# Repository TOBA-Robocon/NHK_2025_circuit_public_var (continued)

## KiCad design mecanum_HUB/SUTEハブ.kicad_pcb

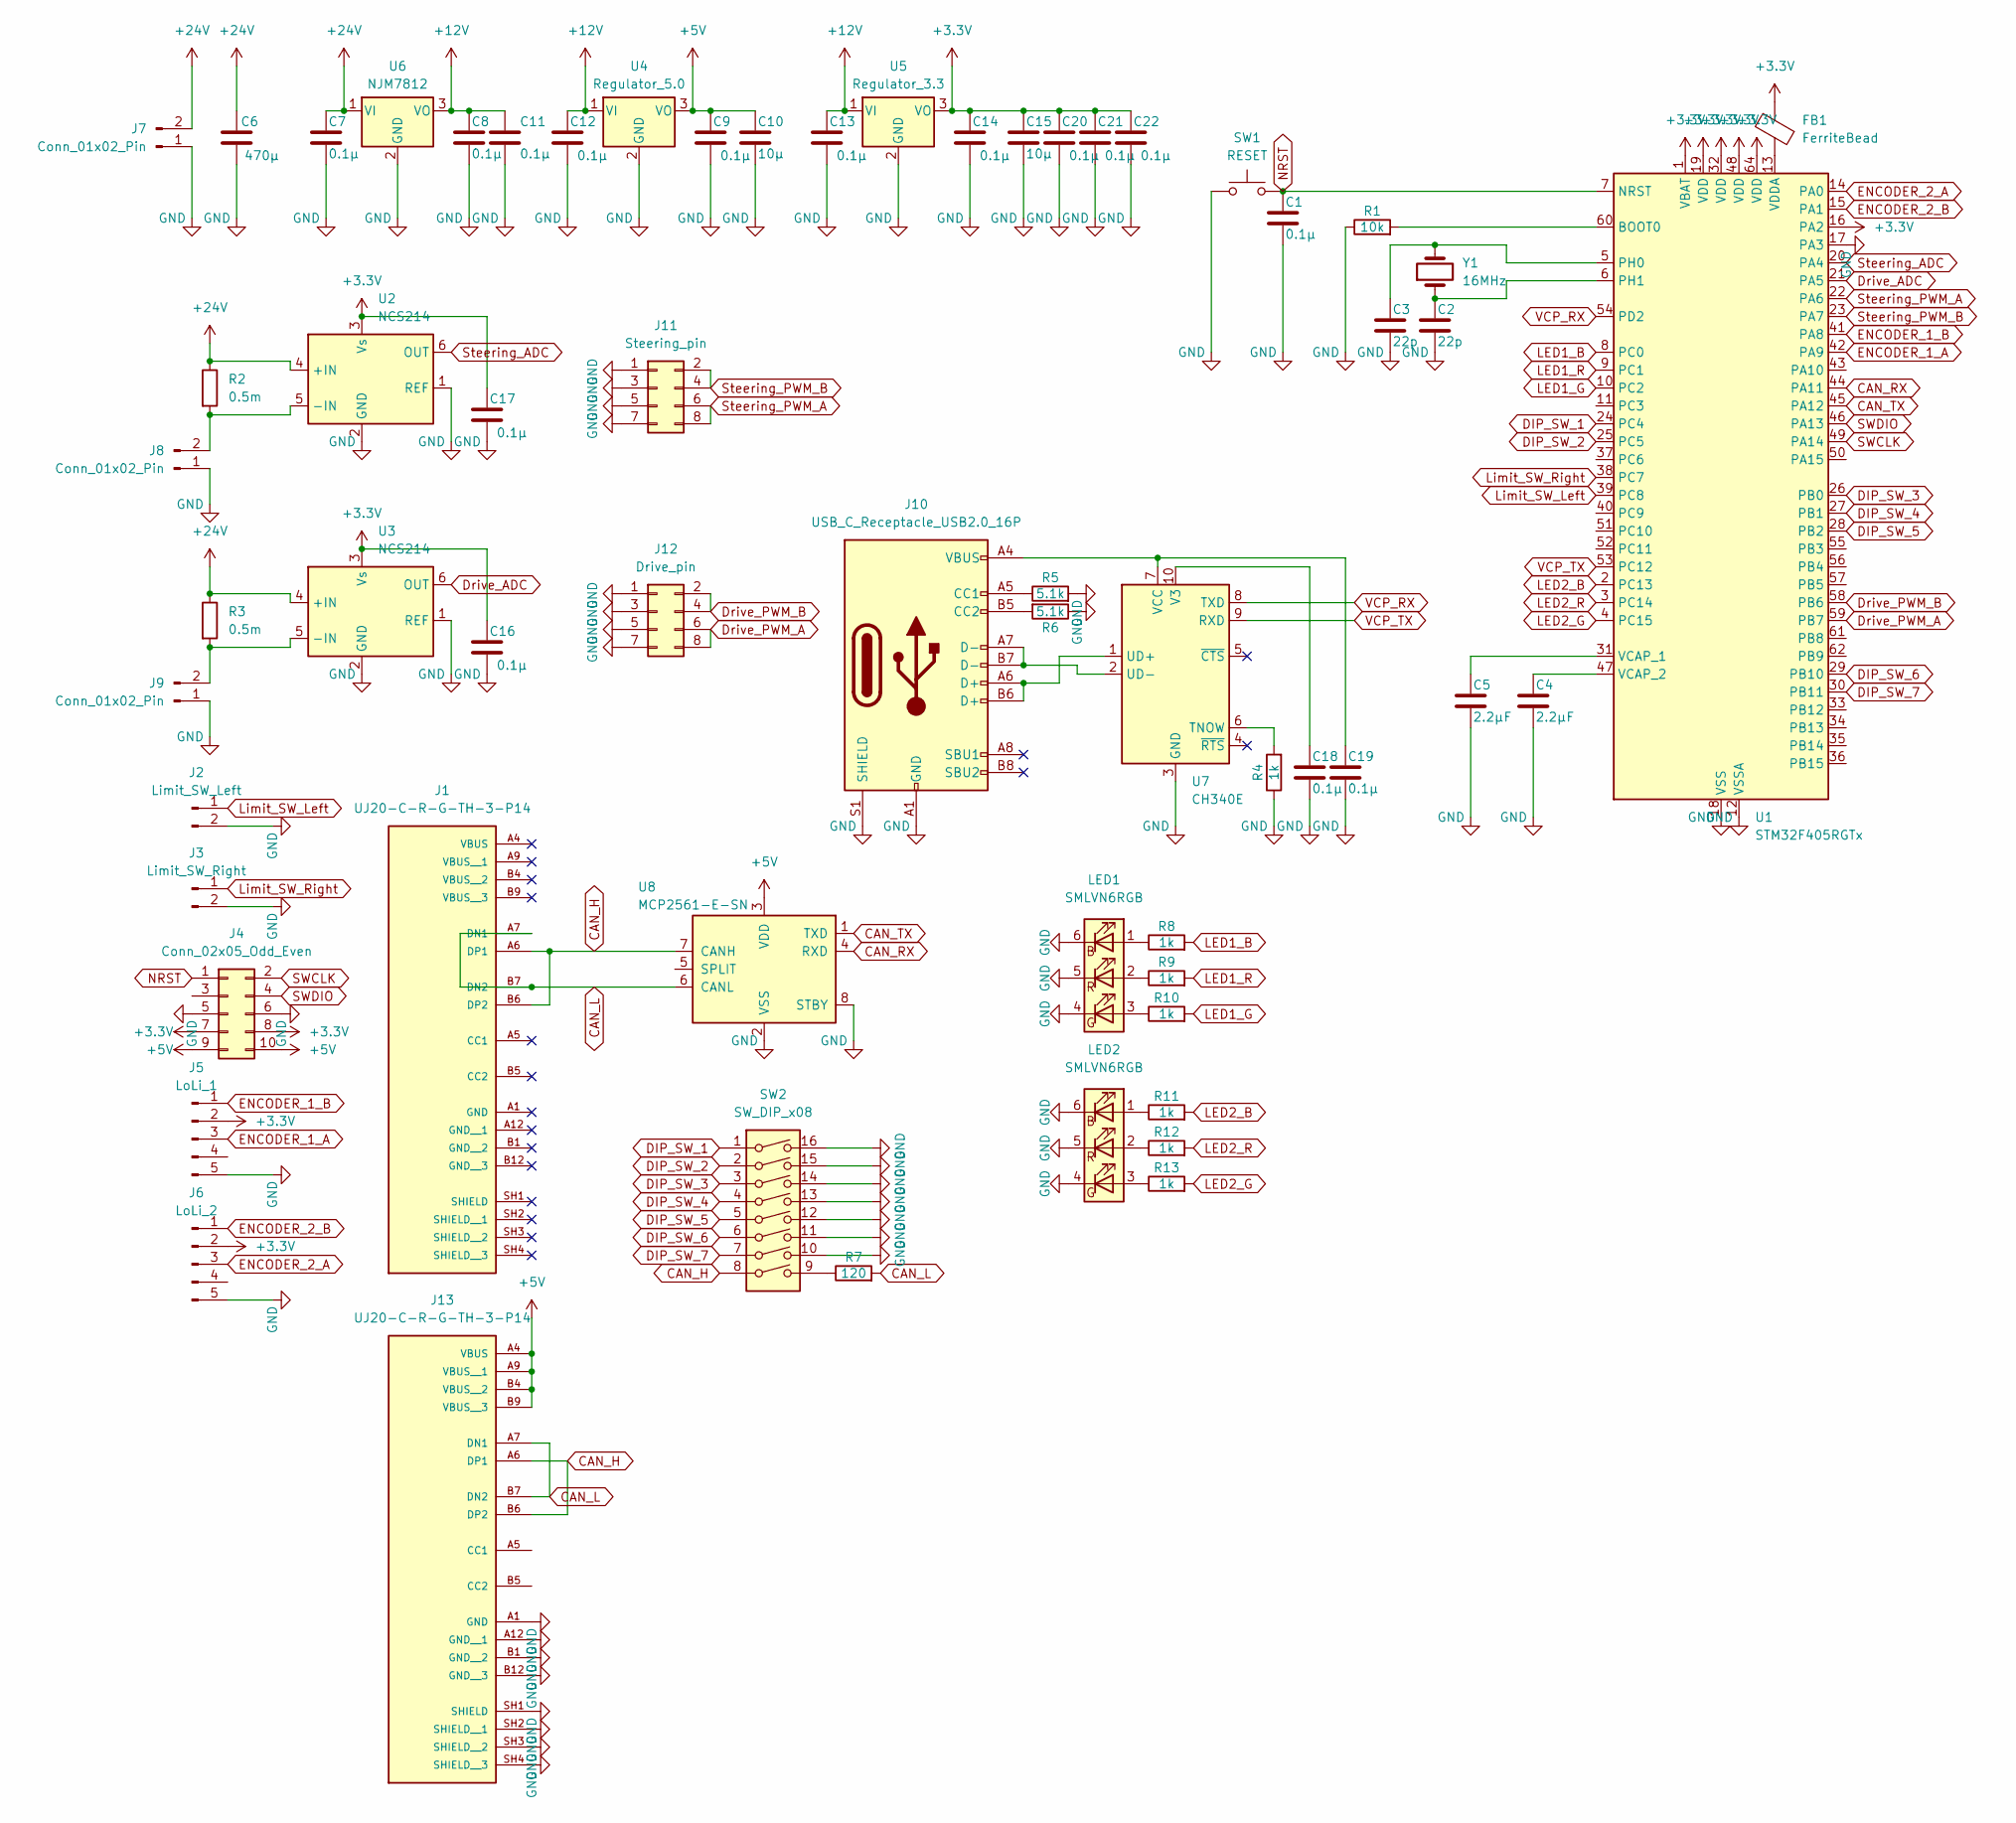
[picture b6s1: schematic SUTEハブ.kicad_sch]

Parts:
C1, C7, C8, C9, C11, C12, C13, C14, C16, C17, C18, C19, C20, C21, C22: 0.1μ; C_0603_1608Metric_Pad1.08x0.95mm_HandSolder
C2, C3: 22p; C_0603_1608Metric_Pad1.08x0.95mm_HandSolder
C4, C5: 2.2μF; C_0603_1608Metric_Pad1.08x0.95mm_HandSolder
C6: 470μ; CP_Radial_D8.0mm_P5.00mm
C10, C15: 10μ; C_0603_1608Metric_Pad1.08x0.95mm_HandSolder
FB1: FerriteBead; L_0805_2012Metric_Pad1.05x1.20mm_HandSolder
J1, J13: UJ20-C-R-G-TH-3-P14; SAMESKY_UJ20-C-R-G-TH-3-P14; PARTREV 1.0
J2: Limit_SW_Left; JST_XA_B02B-XASK-1_1x02_P2.50mm_Vertical
J3: Limit_SW_Right; JST_XA_B02B-XASK-1_1x02_P2.50mm_Vertical
J4: Conn_02x05_Odd_Even; IDC-Header_2x05_P2.54mm_Vertical
J5: LoLi_1; JST_XA_B05B-XASK-1_1x05_P2.50mm_Vertical
J6: LoLi_2; JST_XA_B05B-XASK-1_1x05_P2.50mm_Vertical
J7: Conn_01x02_Pin; AMASS_XT60PW-M_1x02_P7.20mm_Horizontal
J8, J9: Conn_01x02_Pin; AMASS_XT60-F_1x02_P7.20mm_Vertical
J10: USB_C_Receptacle_USB2.0_16P; USB_C_Receptacle_HRO_TYPE-C-31-M-12
J11: Steering_pin; PinSocket_2x04_P2.54mm_Vertical
J12: Drive_pin; PinSocket_2x04_P2.54mm_Vertical
LED1, LED2: SMLVN6RGB; LED_ROHM_SMLVN6
R1: 10k; R_0603_1608Metric_Pad0.98x0.95mm_HandSolder
R2, R3: 0.5m; R_2512_6332Metric
R4, R8, R9, R10, R11, R12, R13: 1k; R_0603_1608Metric_Pad0.98x0.95mm_HandSolder
R5, R6: 5.1k; R_0603_1608Metric_Pad0.98x0.95mm_HandSolder
R7: 120; R_0603_1608Metric_Pad0.98x0.95mm_HandSolder
SW1: RESET; SW_PUSH_6mm
SW2: SW_DIP_x08; DIP-16_W7.62mm
U1: STM32F405RGTx; LQFP-64_10x10mm_P0.5mm
U2, U3: NCS214; SOT-363_SC-70-6_Handsoldering
U4: Regulator_5.0; TO-252-2
U5: Regulator_3.3; TO-252-2
U6: NJM7812; TO-252-2
U7: CH340E; MSOP-10_3x3mm_P0.5mm
U8: MCP2561-E-SN; SOIC-8_3.9x4.9mm_P1.27mm
Y1: 16MHz; Crystal_HC18-U_Vertical

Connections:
+3.3V: C14.1, C15.1, C16.1, C17.1, C20.1, C21.1, C22.1, FB1.2, J4.7, J4.8, J5.2, J6.2, U1.1 (VBAT), U1.16 (PA2), U1.19 (VDD), U1.32 (VDD), U1.48 (VDD), U1.64 (VDD), U2.3 (Vs), U3.3 (Vs), U5.3 (VO)
+5V: C9.1, C10.1, J4.9, J4.10, J13.A4 (VBUS), J13.A9 (VBUS__1), J13.B4 (VBUS__2), J13.B9 (VBUS__3), U4.3 (VO), U8.3 (VDD)
+12V: C8.1, C11.1, C12.1, C13.1, U4.1 (VI), U5.1 (VI), U6.3 (VO)
+24V: C6.1, C7.1, J7.2, R2.1, R3.1, U2.4 (+IN), U3.4 (+IN), U6.1 (VI)
CAN_H: J1.A6 (DP1), J1.B6 (DP2), J13.A6 (DP1), J13.B6 (DP2), SW2.8, U8.7 (CANH)
CAN_L: J1.A7 (DN1), J1.B7 (DN2), J13.A7 (DN1), J13.B7 (DN2), R7.2, U8.6 (CANL)
CAN_RX: U1.44 (PA11), U8.4 (RXD)
CAN_TX: U1.45 (PA12), U8.1 (TXD)
DIP_SW_1: SW2.1, U1.24 (PC4)
DIP_SW_2: SW2.2, U1.25 (PC5)
DIP_SW_3: SW2.3, U1.26 (PB0)
DIP_SW_4: SW2.4, U1.27 (PB1)
DIP_SW_5: SW2.5, U1.28 (PB2)
DIP_SW_6: SW2.6, U1.29 (PB10)
DIP_SW_7: SW2.7, U1.30 (PB11)
Drive_ADC: U1.21 (PA5), U3.6 (OUT)
Drive_PWM_A: J12.6, J12.8, U1.59 (PB7)
Drive_PWM_B: J12.2, J12.4, U1.58 (PB6)
ENCODER_1_A: J5.3, U1.42 (PA9)
ENCODER_1_B: J5.1, U1.41 (PA8)
ENCODER_2_A: J6.3, U1.14 (PA0)
ENCODER_2_B: J6.1, U1.15 (PA1)
GND: C1.2, C2.2, C3.2, C4.2, C5.2, C6.2, C7.2, C8.2, C9.2, C10.2, C11.2, C12.2, C13.2, C14.2, C15.2, C16.2, C17.2, C18.2, C19.2, C20.2, C21.2, C22.2, J2.2, J3.2, J4.5, J4.6, J5.5, J6.5, J7.1, J8.1, J9.1, J10.A1 (GND), J10.A12 (GND), J10.B1 (GND), J10.B12 (GND), J10.S1 (SHIELD), J11.1, J11.3, J11.5, J11.7, J12.1, J12.3, J12.5, J12.7, J13.A1 (GND), J13.A12 (GND__1), J13.B1 (GND__2), J13.B12 (GND__3), J13.SH1 (SHIELD), J13.SH2 (SHIELD__1), J13.SH3 (SHIELD__2), J13.SH4 (SHIELD__3), LED1.4 (GK), LED1.5 (RK), LED1.6 (BK), LED2.4 (GK), LED2.5 (RK), LED2.6 (BK), R1.1, R4.1, R5.2, R6.1, SW1.1, SW2.10, SW2.11, SW2.12, SW2.13, SW2.14, SW2.15, SW2.16, U1.12 (VSSA), U1.17 (PA3), U1.18 (VSS), U1.63 (VSS), U2.1 (REF), U2.2 (GND), U3.1 (REF), U3.2 (GND), U4.2 (GND), U5.2 (GND), U6.2 (GND), U7.3 (GND), U8.2 (VSS), U8.8 (STBY)
LED1_B: R8.2, U1.8 (PC0)
LED1_G: R10.2, U1.10 (PC2)
LED1_R: R9.2, U1.9 (PC1)
LED2_B: R11.2, U1.2 (PC13)
LED2_G: R13.2, U1.4 (PC15)
LED2_R: R12.2, U1.3 (PC14)
Limit_SW_Left: J2.1, U1.39 (PC8)
Limit_SW_Right: J3.1, U1.38 (PC7)
NRST: C1.1, J4.1, SW1.2, U1.7 (NRST)
unnamed: J8.2, R2.2, U2.5 (-IN)
unnamed: J9.2, R3.2, U3.5 (-IN)
unnamed: J10.A5 (CC1), R5.1
unnamed: J10.B5 (CC2), R6.2
unnamed: LED1.1 (BA), R8.1
unnamed: LED1.3 (GA), R10.1
unnamed: LED1.2 (RA), R9.1
unnamed: LED2.1 (BA), R11.1
unnamed: LED2.3 (GA), R13.1
unnamed: LED2.2 (RA), R12.1
unnamed: R7.1, SW2.9
unnamed: R1.2, U1.60 (BOOT0)
unnamed: C3.1, U1.5 (PH0), Y1.2
unnamed: C2.1, U1.6 (PH1), Y1.1
unnamed: C5.1, U1.31 (VCAP_1)
unnamed: C4.1, U1.47 (VCAP_2)
unnamed: FB1.1, U1.13 (VDDA)
unnamed: R4.2, U7.6 (TNOW)
unnamed: J10.A6 (D+), J10.B6 (D+), U7.1 (UD+)
unnamed: J10.A7 (D-), J10.B7 (D-), U7.2 (UD-)
unnamed: C18.1, U7.10 (V3)
unnamed: C19.1, J10.A4 (VBUS), J10.A9 (VBUS), J10.B4 (VBUS), J10.B9 (VBUS), U7.7 (VCC)
SWCLK: J4.2, U1.49 (PA14)
SWDIO: J4.4, U1.46 (PA13)
Steering_ADC: U1.20 (PA4), U2.6 (OUT)
Steering_PWM_A: J11.6, J11.8, U1.22 (PA6)
Steering_PWM_B: J11.2, J11.4, U1.23 (PA7)
VCP_RX: U1.54 (PD2), U7.8 (TXD)
VCP_TX: U1.53 (PC12), U7.9 (RXD)

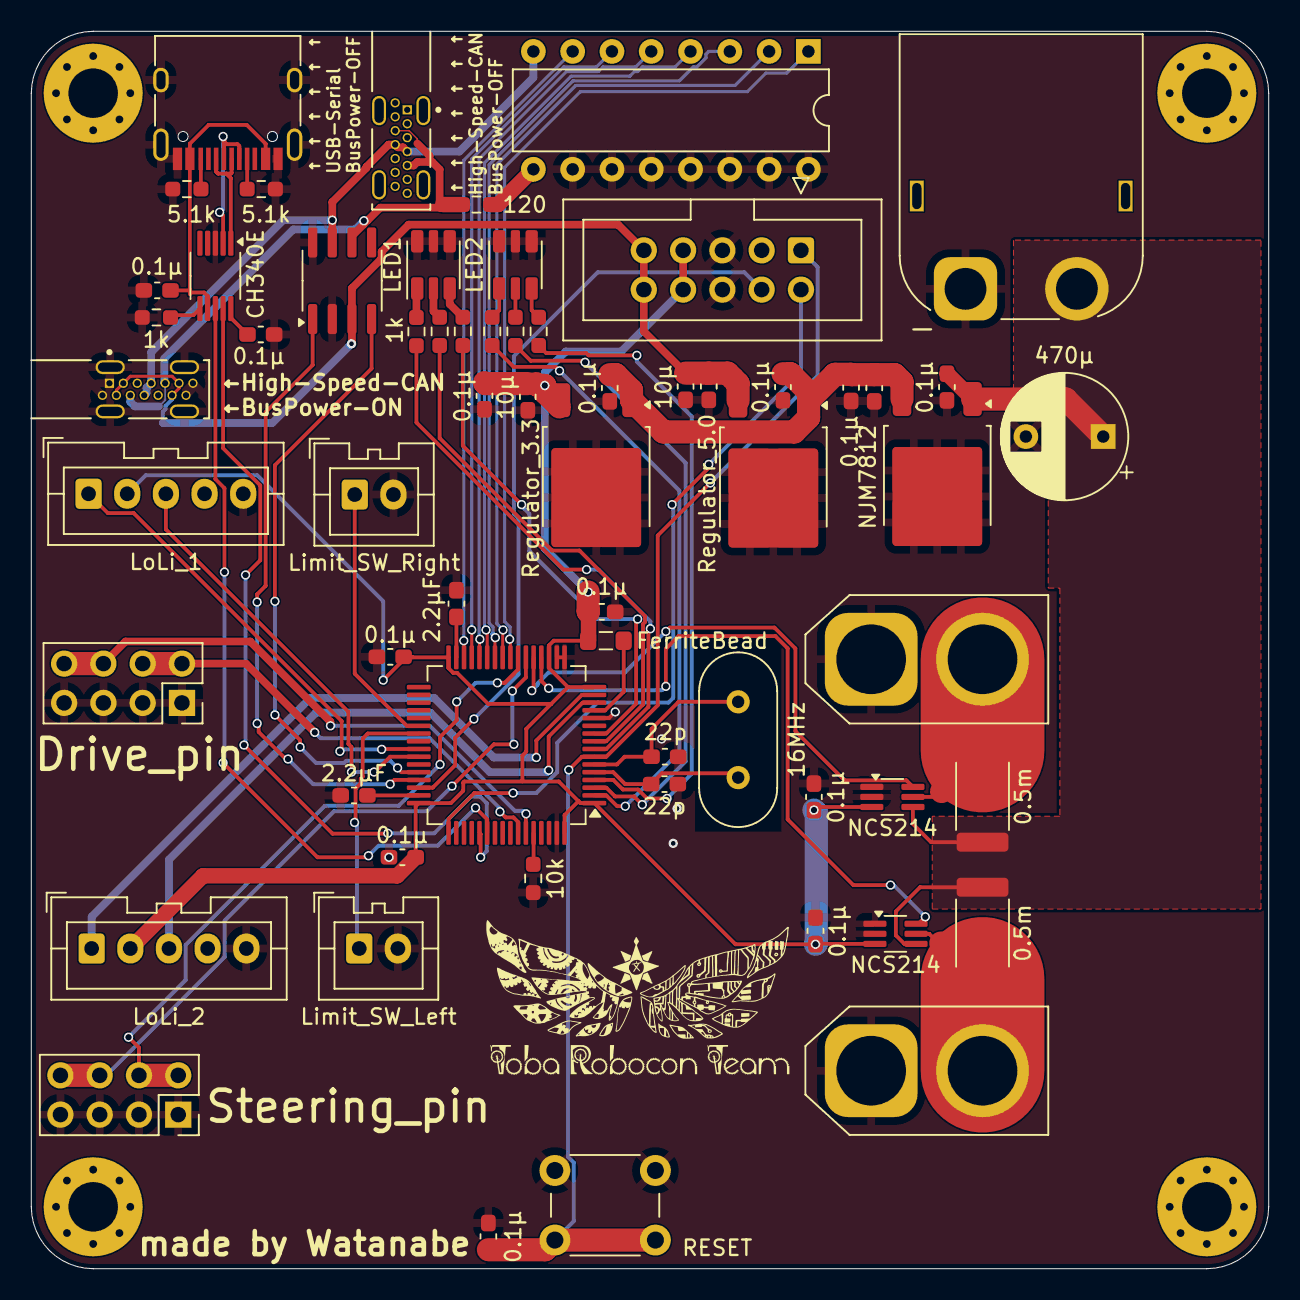
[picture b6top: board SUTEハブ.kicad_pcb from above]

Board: 2 copper layers, 80.0 x 80.0 mm, 62 parts (0 on the bottom side), 61 nets.

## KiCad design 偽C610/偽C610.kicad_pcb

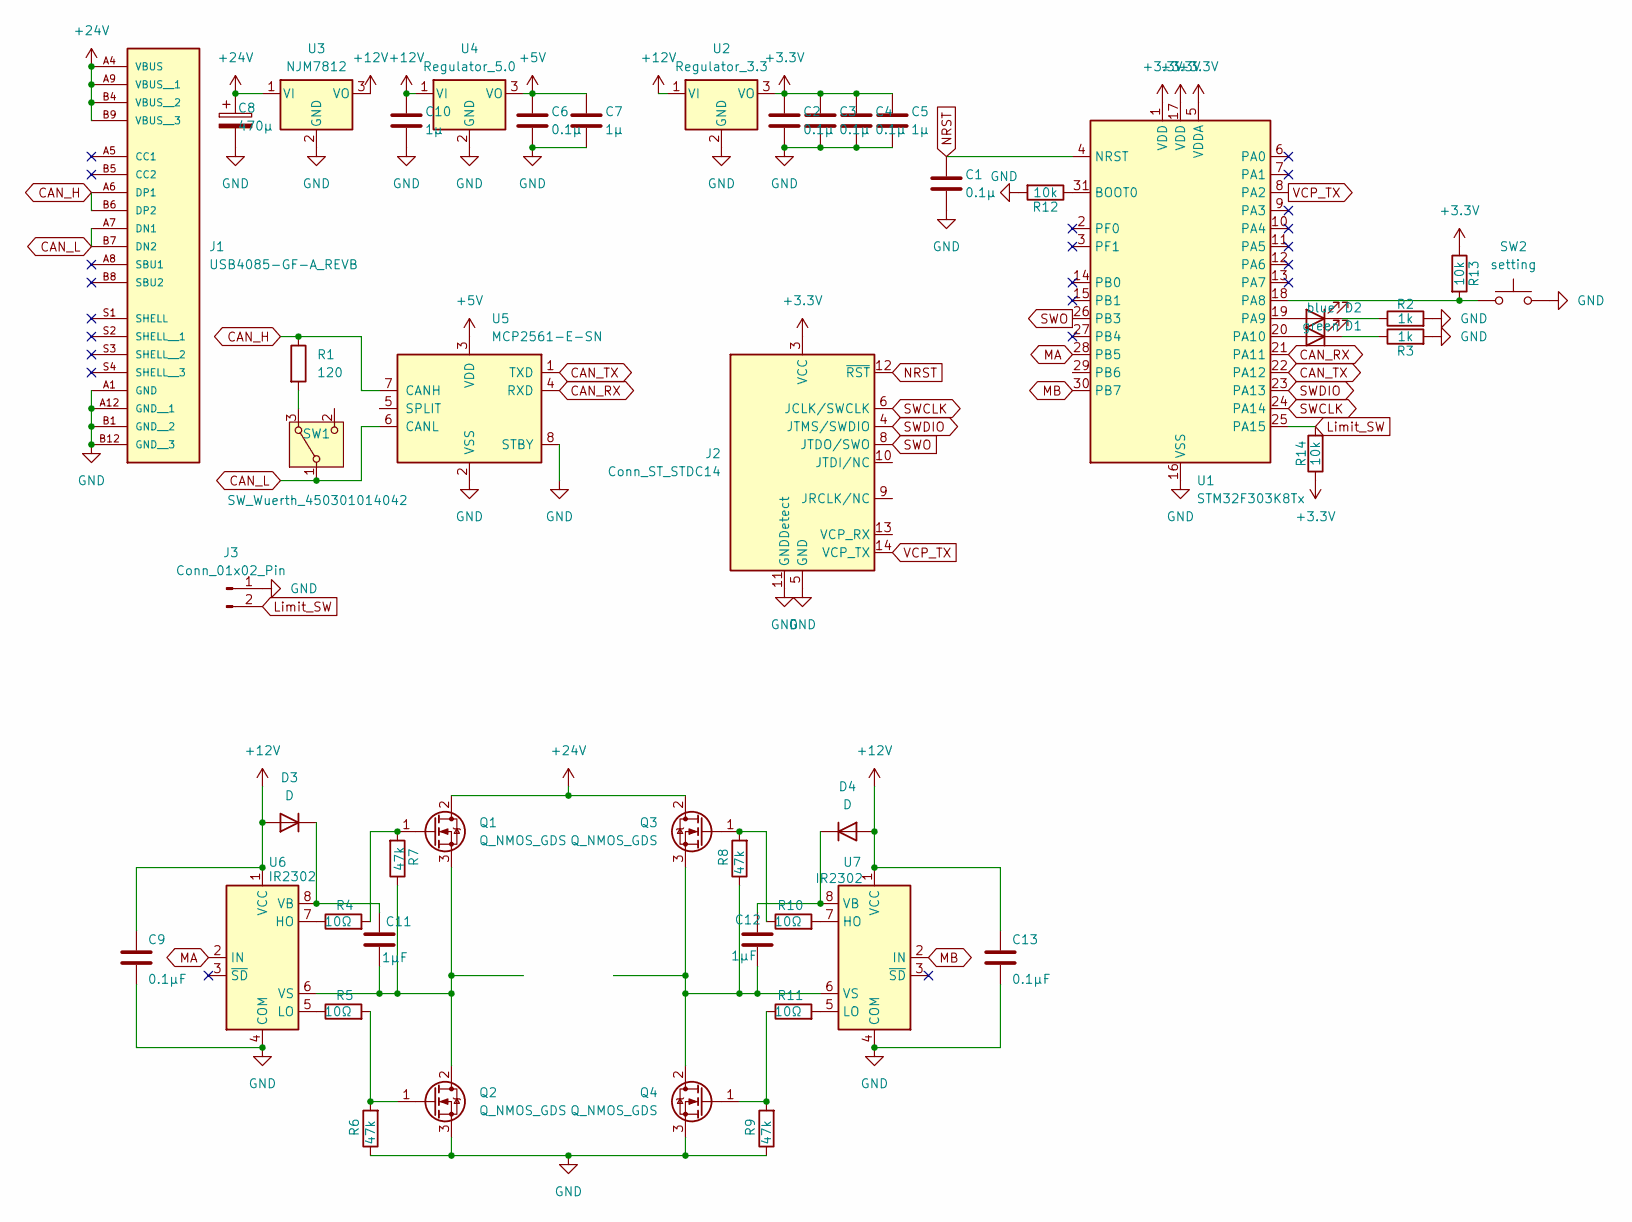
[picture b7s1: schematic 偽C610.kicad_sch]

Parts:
C1, C2, C3, C4, C6: 0.1μ; C_0603_1608Metric
C5, C7, C10: 1μ; C_0603_1608Metric
C8: 470μ; CP_Radial_D8.0mm_P3.50mm
C9, C13: 0.1μF; C_0603_1608Metric_Pad1.08x0.95mm_HandSolder
C11, C12: 1μF; C_0603_1608Metric_Pad1.08x0.95mm_HandSolder
D1: green; LED_0603_1608Metric
D2: blue; LED_0603_1608Metric
D3, D4: D; D_SOD-123F
J1: USB4085-GF-A_REVB; GCT_USB4085-GF-A_REVB; PARTREV B
J2: Conn_ST_STDC14; PinHeader_2x07_P1.27mm_Vertical
J3: Conn_01x02_Pin; JST_PH_B2B-PH-SM4-TB_1x02-1MP_P2.00mm_Vertical
Q1, Q2, Q3, Q4: Q_NMOS_GDS; TO-252-2
R1: 120; R_0603_1608Metric
R2, R3: 1k; R_0603_1608Metric
R4, R5, R10, R11: 10Ω; R_0603_1608Metric_Pad0.98x0.95mm_HandSolder
R6, R7, R8, R9: 47k; R_0603_1608Metric_Pad0.98x0.95mm_HandSolder
R12, R13, R14: 10k; R_0603_1608Metric
SW1: SW_Wuerth_450301014042; SW_Slide-03_Wuerth-WS-SLTV_10x2.5x6.4_P2.54mm
SW2: setting; SW_PUSH_1P1T_6x3.5mm_H5.0_APEM_MJTP1250
U1: STM32F303K8Tx; LQFP-32_7x7mm_P0.8mm
U2: Regulator_3.3; TO-252-2
U3: NJM7812; TO-252-2
U4: Regulator_5.0; TO-252-2
U5: MCP2561-E-SN; SOIC-8_3.9x4.9mm_P1.27mm
U6, U7: IR2302; SOIC-8_3.9x4.9mm_P1.27mm

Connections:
+3.3V: C2.1, C3.1, C4.1, C5.1, J2.3 (VCC), R13.1, R14.1, U1.1 (VDD), U1.5 (VDDA), U1.17 (VDD), U2.3 (VO)
+5V: C6.1, C7.1, U4.3 (VO), U5.3 (VDD)
+12V: C9.1, C10.1, C13.1, D3.2 (A), D4.2 (A), U2.1 (VI), U3.3 (VO), U4.1 (VI), U6.1 (VCC), U7.1 (VCC)
+24V: C8.1, J1.A4 (VBUS), J1.A9 (VBUS__1), J1.B4 (VBUS__2), J1.B9 (VBUS__3), Q1.2 (D), Q3.2 (D), U3.1 (VI)
CAN_H: J1.A6 (DP1), J1.B6 (DP2), R1.1, U5.7 (CANH)
CAN_L: J1.A7 (DN1), J1.B7 (DN2), SW1.1 (B), U5.6 (CANL)
CAN_RX: U1.21 (PA11), U5.4 (RXD)
CAN_TX: U1.22 (PA12), U5.1 (TXD)
GND: C1.2, C2.2, C3.2, C4.2, C5.2, C6.2, C7.2, C8.2, C9.2, C10.2, C13.2, J1.A1 (GND), J1.A12 (GND__1), J1.B1 (GND__2), J1.B12 (GND__3), J2.5 (GND), J2.7 (GND), J2.11 (GNDDetect), J3.1, Q2.3 (S), Q4.3 (S), R2.2, R3.2, R6.1, R9.1, R12.2, SW2.2, U1.16 (VSS), U1.32 (VSS), U2.2 (GND), U3.2 (GND), U4.2 (GND), U5.2 (VSS), U5.8 (STBY), U6.4 (COM), U7.4 (COM)
Limit_SW: J3.2, R14.2, U1.25 (PA15)
MA: U1.28 (PB5), U6.2 (IN)
MB: U1.30 (PB7), U7.2 (IN)
NRST: C1.1, J2.12 (~RST), U1.4 (NRST)
unnamed: D1.2 (A), U1.20 (PA10)
unnamed: D1.1 (K), R3.1
unnamed: D2.2 (A), U1.19 (PA9)
unnamed: D2.1 (K), R2.1
unnamed: C11.1, D3.1 (K), U6.8 (VB)
unnamed: C12.1, D4.1 (K), U7.8 (VB)
unnamed: Q1.1 (G), R4.2, R7.2
unnamed: C11.2, Q1.3 (S), Q2.2 (D), R7.1, U6.6 (VS)
unnamed: Q2.1 (G), R5.2, R6.2
unnamed: Q3.1 (G), R8.2, R10.1
unnamed: C12.2, Q3.3 (S), Q4.2 (D), R8.1, U7.6 (VS)
unnamed: Q4.1 (G), R9.2, R11.1
unnamed: R1.2, SW1.3 (A)
unnamed: R12.1, U1.31 (BOOT0)
unnamed: R13.2, SW2.1, U1.18 (PA8)
unnamed: R4.1, U6.7 (HO)
unnamed: R5.1, U6.5 (LO)
unnamed: R10.2, U7.7 (HO)
unnamed: R11.2, U7.5 (LO)
SWCLK: J2.6 (JCLK/SWCLK), U1.24 (PA14)
SWDIO: J2.4 (JTMS/SWDIO), U1.23 (PA13)
SWO: J2.8 (JTDO/SWO), U1.26 (PB3)
VCP_TX: J2.14 (VCP_TX), U1.8 (PA2)

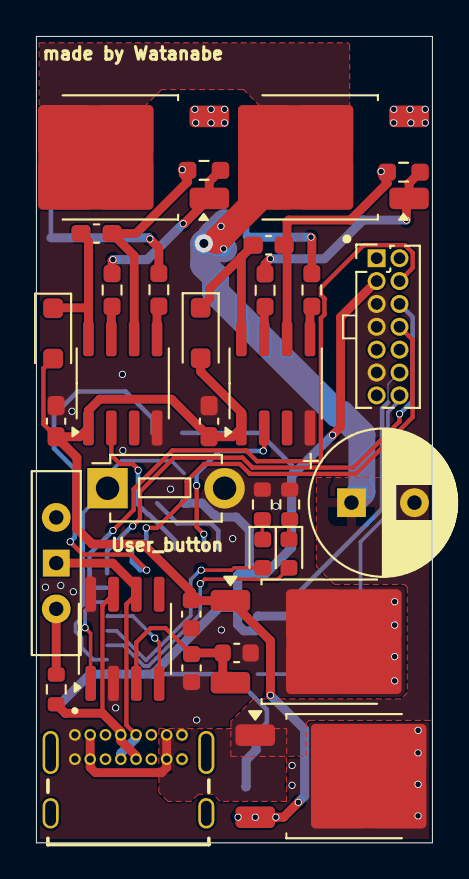
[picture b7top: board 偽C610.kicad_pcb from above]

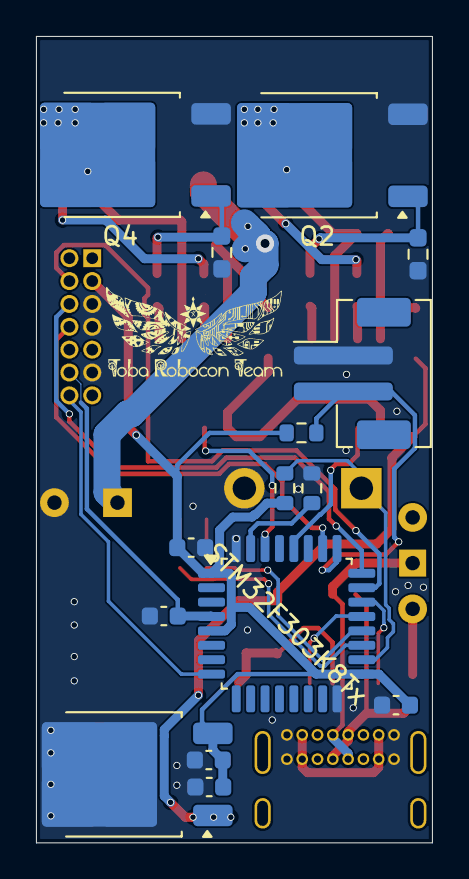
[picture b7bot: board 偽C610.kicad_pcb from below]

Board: 2 copper layers, 22.0 x 44.8 mm, 47 parts (15 on the bottom side), 36 nets.

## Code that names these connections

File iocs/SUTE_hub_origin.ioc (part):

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Mcu.Name=STM32F405RGTx
Mcu.Package=LQFP64
Mcu.UserName=STM32F405RGTx
PA0-WKUP.GPIOParameters=GPIO_PuPd,GPIO_Label
PA0-WKUP.GPIO_Label=ENCODER_2_A
PA0-WKUP.GPIO_PuPd=GPIO_PULLDOWN
PA0-WKUP.Signal=S_TIM2_CH1_ETR
PA1.GPIOParameters=GPIO_PuPd,GPIO_Label
PA1.GPIO_Label=ENCODER_2_B
PA1.GPIO_PuPd=GPIO_PULLDOWN
PA1.Signal=S_TIM2_CH2
PA11.Mode=CAN_Activate
PA11.Signal=CAN1_RX
PA12.Mode=CAN_Activate
PA12.Signal=CAN1_TX
PA13.Mode=Serial_Wire
PA13.Signal=SYS_JTMS-SWDIO
PA14.Mode=Serial_Wire
PA14.Signal=SYS_JTCK-SWCLK
PA2.GPIOParameters=GPIO_Label
PA2.GPIO_Label=Vdd_ADC
PA2.Signal=ADCx_IN2
PA3.GPIOParameters=GPIO_Label
PA3.GPIO_Label=GND_ADC
PA3.Signal=ADCx_IN3
PA4.GPIOParameters=GPIO_Label
PA4.GPIO_Label=Steering_current
PA4.Signal=ADCx_IN4
PA5.GPIOParameters=GPIO_Label
PA5.GPIO_Label=Drive_current
PA5.Signal=ADCx_IN5
PA6.GPIOParameters=GPIO_Label
PA6.GPIO_Label=Steering_A
PA6.Signal=S_TIM3_CH1
PA7.GPIOParameters=GPIO_Label
PA7.GPIO_Label=Steering_B
PA7.Signal=S_TIM3_CH2
PA8.GPIOParameters=GPIO_PuPd,GPIO_Label
PA8.GPIO_Label=ENCODER_1_B
PA8.GPIO_PuPd=GPIO_PULLDOWN
PA8.Signal=S_TIM1_CH1
PA9.GPIOParameters=GPIO_PuPd,GPIO_Label
PA9.GPIO_Label=ENCODER_1_A
PA9.GPIO_PuPd=GPIO_PULLDOWN
PA9.Signal=S_TIM1_CH2
PB0.GPIOParameters=GPIO_PuPd,GPIO_Label
PB0.GPIO_Label=DIP_SW_3
PB0.GPIO_PuPd=GPIO_PULLUP
PB0.Signal=GPIO_Input
PB1.GPIOParameters=GPIO_PuPd,GPIO_Label
PB1.GPIO_Label=DIP_SW_4
PB1.GPIO_PuPd=GPIO_PULLUP
PB1.Signal=GPIO_Input
PB10.GPIOParameters=GPIO_PuPd,GPIO_Label
PB10.GPIO_Label=DIP_SW_6
PB10.GPIO_PuPd=GPIO_PULLUP
PB10.Signal=GPIO_Input
PB11.GPIOParameters=GPIO_PuPd,GPIO_Label
PB11.GPIO_Label=DIP_SW_7
PB11.GPIO_PuPd=GPIO_PULLUP
PB11.Signal=GPIO_Input
PB2.GPIOParameters=GPIO_PuPd,GPIO_Label
PB2.GPIO_Label=DIP_SW_5
PB2.GPIO_PuPd=GPIO_PULLUP
PB2.Signal=GPXTI2
PB6.GPIOParameters=GPIO_Label
PB6.GPIO_Label=Drive_B
PB6.Signal=S_TIM4_CH1
PB7.GPIOParameters=GPIO_Label
PB7.GPIO_Label=Drive_A
PB7.Signal=S_TIM4_CH2
PC0.GPIOParameters=GPIO_Label
PC0.GPIO_Label=LED1_B
PC0.Signal=GPIO_Output
PC1.GPIOParameters=GPIO_Label
PC1.GPIO_Label=LED1_R
PC1.Signal=GPIO_Output
PC12.Mode=Asynchronous
PC12.Signal=UART5_TX
PC13-ANTI_TAMP.GPIOParameters=GPIO_Label
PC13-ANTI_TAMP.GPIO_Label=LED2_B
PC13-ANTI_TAMP.Signal=GPIO_Output
PC14-OSC32_IN.GPIOParameters=GPIO_Label
PC14-OSC32_IN.GPIO_Label=LED2_R
PC14-OSC32_IN.Signal=GPIO_Output
PC15-OSC32_OUT.GPIOParameters=GPIO_Label
PC15-OSC32_OUT.GPIO_Label=LED2_G
PC15-OSC32_OUT.Signal=GPIO_Output
PC2.GPIOParameters=GPIO_Label
PC2.GPIO_Label=LED1_G
PC2.Signal=GPIO_Output
PC4.GPIOParameters=GPIO_PuPd,GPIO_Label
PC4.GPIO_Label=DIP_SW_1
PC4.GPIO_PuPd=GPIO_PULLUP
PC4.Signal=GPIO_Input
PC5.GPIOParameters=GPIO_PuPd,GPIO_Label
PC5.GPIO_Label=DIP_SW_2
PC5.GPIO_PuPd=GPIO_PULLUP
PC5.Signal=GPIO_Input
PC7.GPIOParameters=GPIO_PuPd,GPIO_Label
PC7.GPIO_Label=Limit_SW_Right
PC7.GPIO_PuPd=GPIO_PULLUP
PC7.Signal=GPXTI7
PC8.GPIOParameters=GPIO_PuPd,GPIO_Label
PC8.GPIO_Label=Limit_SW_Left
PC8.GPIO_PuPd=GPIO_PULLUP
PC8.Signal=GPXTI8
PD2.Mode=Asynchronous
PD2.Signal=UART5_RX
PH0-OSC_IN.Mode=HSE-External-Oscillator
PH0-OSC_IN.Signal=RCC_OSC_IN
PH1-OSC_OUT.Mode=HSE-External-Oscillator
PH1-OSC_OUT.Signal=RCC_OSC_OUT
RCC.HSE_VALUE=16000000
RCC.SYSCLKFreq_VALUE=120000000
RCC.SYSCLKSource=RCC_SYSCLKSOURCE_PLLCLK
board=custom

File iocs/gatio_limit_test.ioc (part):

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Mcu.Name=STM32F303K(6-8)Tx
Mcu.Package=LQFP32
Mcu.UserName=STM32F303K8Tx
PA0.Mode=IN1-Single-Ended
PA0.Signal=ADC1_IN1
PA1.GPIOParameters=GPIO_PuPd,GPIO_Label
PA1.GPIO_Label=Encoder_B
PA1.GPIO_PuPd=GPIO_PULLDOWN
PA1.Signal=S_TIM2_CH2
PA10.Mode=Asynchronous
PA10.Signal=USART1_RX
PA11.Mode=CAN_Activate
PA11.Signal=CAN_RX
PA12.Mode=CAN_Activate
PA12.Signal=CAN_TX
PA13.Mode=Trace_Asynchronous_SW
PA13.Signal=SYS_JTMS-SWDIO
PA14.Mode=Trace_Asynchronous_SW
PA14.Signal=SYS_JTCK-SWCLK
PA15.GPIOParameters=GPIO_Label
PA15.GPIO_Label=LED2_R
PA15.Signal=GPIO_Output
PA2.GPIOParameters=GPIO_Label
PA2.GPIO_Label=user_button_1
PA2.Signal=GPIO_Input
PA3.GPIOParameters=GPIO_Label
PA3.GPIO_Label=user_button_2
PA3.Signal=GPIO_Input
PA5.GPIOParameters=GPIO_PuPd,GPIO_Label
PA5.GPIO_Label=Encoder_A
PA5.GPIO_PuPd=GPIO_PULLDOWN
PA5.Signal=S_TIM2_CH1_ETR
PA7.Signal=S_TIM3_CH2
PA8.GPIOParameters=GPIO_Label
PA8.GPIO_Label=LED2_G_2
PA8.Signal=GPIO_Output
PA9.Mode=Asynchronous
PA9.Signal=USART1_TX
PB0.Signal=S_TIM3_CH3
PB1.GPIOParameters=GPIO_Label
PB1.GPIO_Label=limit_SW
PB1.Signal=GPIO_Input
PB3.Mode=Trace_Asynchronous_SW
PB3.Signal=SYS_JTDO-TRACESWO
PB4.GPIOParameters=GPIO_Label
PB4.GPIO_Label=LED2_G_1
PB4.Signal=GPIO_Output
PB5.GPIOParameters=GPIO_Label
PB5.GPIO_Label=LED1_G
PB5.Signal=GPIO_Output
PB6.GPIOParameters=GPIO_Label
PB6.GPIO_Label=LED1_R
PB6.Signal=GPIO_Output
PB7.GPIOParameters=GPIO_Label
PB7.GPIO_Label=LED1_B
PB7.Signal=GPIO_Output
PF0\ /\ OSC_IN.Mode=HSE-External-Oscillator
PF0\ /\ OSC_IN.Signal=RCC_OSC_IN
PF1\ /\ OSC_OUT.Mode=HSE-External-Oscillator
PF1\ /\ OSC_OUT.Signal=RCC_OSC_OUT
RCC.HSEPLLFreq_Value=4000000
RCC.HSE_VALUE=16000000
RCC.SYSCLKFreq_VALUE=60000000
RCC.SYSCLKSourceVirtual=RCC_SYSCLKSOURCE_PLLCLK
board=custom

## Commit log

2025-10-05 first_commit
2025-10-05 GOD_DC_MDを追加
2025-10-05 iocファイルを追加
2025-10-05 ESP32でDualshock4の値を取得するプログラムを追加
2025-10-05 Dualshock4の値の規格表を追加
